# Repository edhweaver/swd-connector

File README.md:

SWD Connector Circuit Board
--------------------------------------------------------------------------------

  This circuit board was designed to provide a standard SWD Connection for a
Proffie board installed inside a Light Saber chassis.  This board has the
following features incorporated into the design:
  * The SWD connector connects to a standard 2x5 IDC with 1.27 mm pitch
  * Circuits added to protect against signal noise on IDC cable
    * Decoupling capacitor on power
    * Reset Circuit to prevent unexpected reset
    * SWD Circuit added to keep initial signal levels for STM32 family
  * Mounting Holes added for easy installation onto Light Saber chassis

  PCB Revision is on the bottom of the PCB in silkscreen.  PCA Revision has a
silkscreen box to track BOM polulation.

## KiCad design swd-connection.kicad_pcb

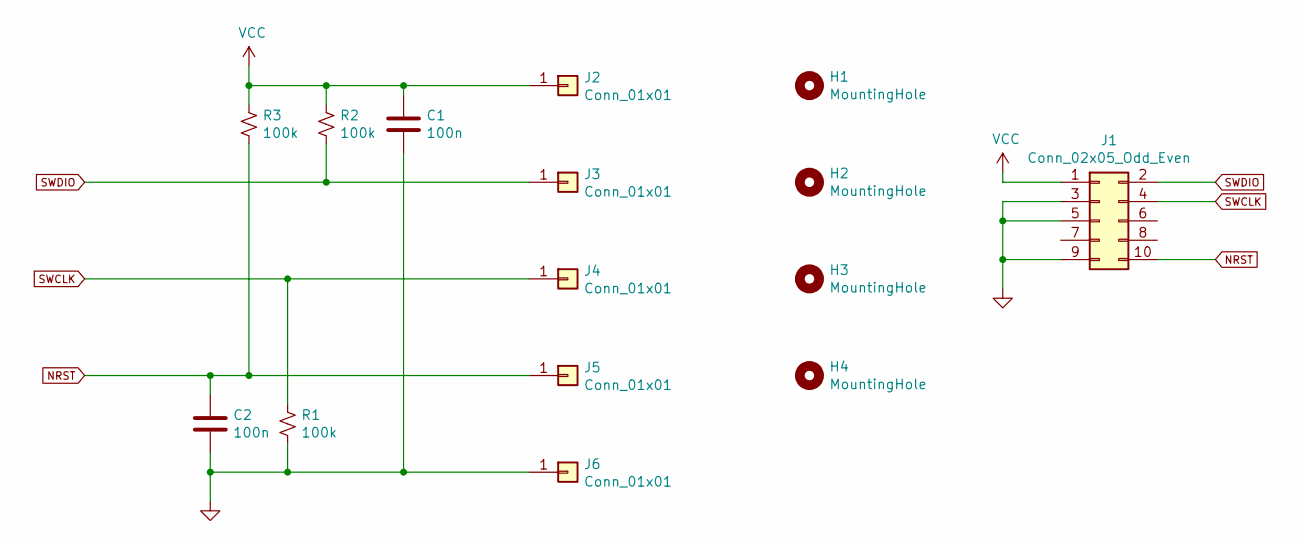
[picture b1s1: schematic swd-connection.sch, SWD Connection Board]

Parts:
C1, C2: 100n; C_0603_1608Metric
H1, H2, H3, H4: MountingHole; MountingHole_2.2mm_M2
J1: Conn_02x05_Odd_Even; ADAFRUIT_752_2X05_1.27MM_BOX_HEADER
J2, J3, J4, J5, J6: Conn_01x01; TestPoint_THTPad_D1.5mm_Drill0.7mm
R1, R2, R3: 100k; R_0603_1608Metric

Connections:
GND: C1.2, C2.2, J1.3, J1.5, J1.9, J6.1, R1.2
NRST: C2.1, J1.10, J5.1, R3.2
SWCLK: J1.4, J4.1, R1.1
SWDIO: J1.2, J3.1, R2.2
VCC: C1.1, J1.1, J2.1, R2.1, R3.1

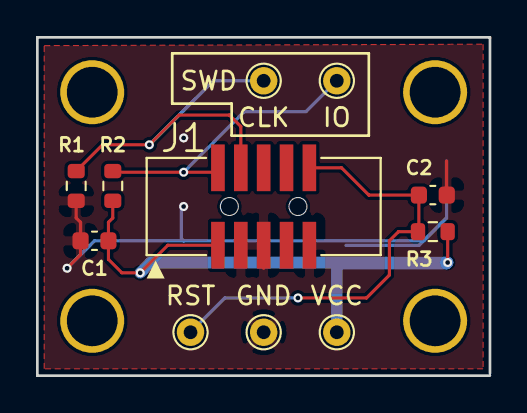
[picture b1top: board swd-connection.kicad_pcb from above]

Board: 2 copper layers, 25.1 x 18.8 mm, 15 parts (0 on the bottom side), 5 nets.

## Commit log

2021-02-22 - Initial Schematic design - Initial Layout design - Footprint Library for Layout - Generate Manufacturing Files
2021-02-22 - Updated Readme
